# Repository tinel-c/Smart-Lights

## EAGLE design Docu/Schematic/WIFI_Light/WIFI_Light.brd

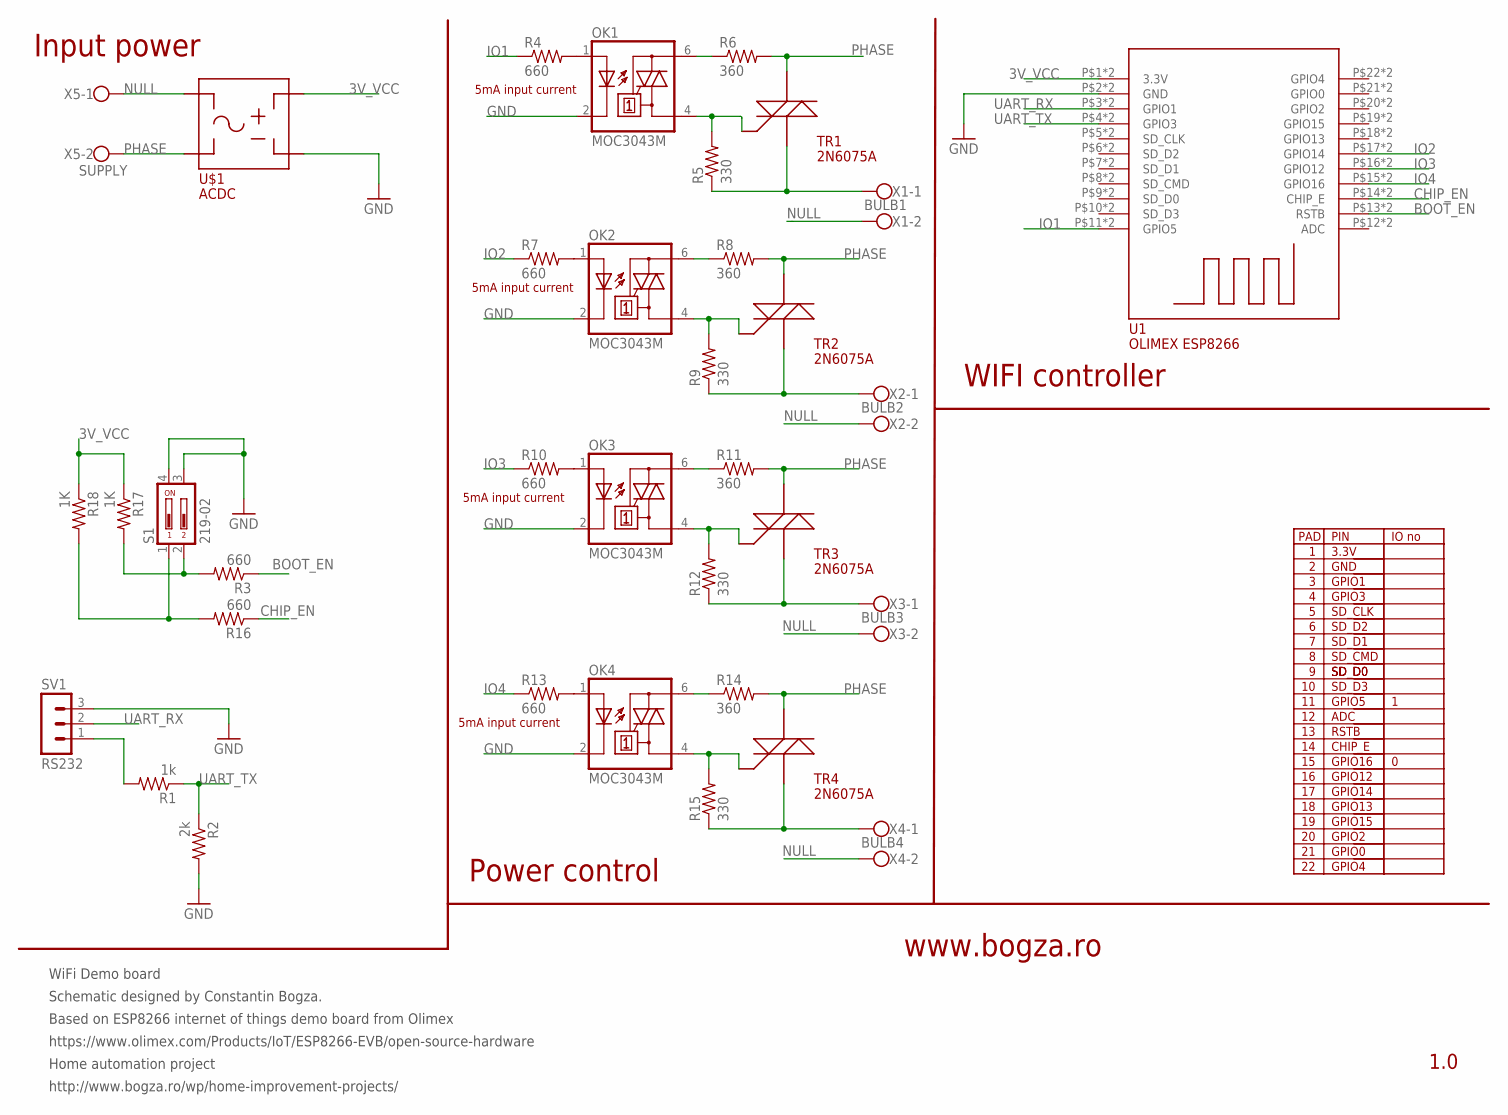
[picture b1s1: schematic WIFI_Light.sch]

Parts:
OK1, OK2, OK3, OK4: MOC3043M; DIL06
R1: 1k; 1206
R2: 2k; 1206
R3, R4, R7, R10, R13, R16: 660; 1206
R5, R9, R12, R15: 330; 1206
R6, R8, R11, R14: 360; 1206
R17, R18: 1K; 1206
S1: 219-02; CTS-219-02
SV1: RS232; MA03-1
TR1, TR2, TR3, TR4: 2N6071A/B; TO–225AA
U1: OLIMEX_ESP8266; OLIMEX_ESP8266_DIP22
U$1: ACDC_220V_3V3
X1: BULB1; W237-102
X2: BULB2; W237-102
X3: BULB3; W237-102
X4: BULB4; W237-102
X5: SUPPLY; W237-102

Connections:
3V_VCC: R17.1, R18.1, U1.P$1 (3.3V), U1.P$23 (3.3V), U$1.VCC
BOOT_EN: R3.1, U1.P$13 (RSTB), U1.P$35 (RSTB)
CHIP_EN: R16.1, U1.P$14 (CHIP_E), U1.P$36 (CHIP_E)
GND: OK1.2 (C), OK2.2 (C), OK3.2 (C), OK4.2 (C), R2.2, S1.3, S1.4, SV1.3, U1.P$2 (GND), U1.P$24 (GND), U$1.GND
IO1: R4.1, U1.P$11 (GPIO5), U1.P$33 (GPIO5)
IO2: R7.1, U1.P$17 (GPIO14), U1.P$39 (GPIO14)
IO3: R10.1, U1.P$16 (GPIO12), U1.P$38 (GPIO12)
IO4: R13.1, U1.P$15 (GPIO16), U1.P$37 (GPIO16)
unnamed: OK1.6 (A2), R6.1
unnamed: OK1.1 (A), R4.2
unnamed: R3.2, R17.2, S1.2
unnamed: R16.2, R18.2, S1.1
unnamed: OK1.4 (A1), R5.2, TR1.G
unnamed: OK2.6 (A2), R8.1
unnamed: R1.2, SV1.1
unnamed: OK2.1 (A), R7.2
unnamed: OK2.4 (A1), R9.2, TR2.G
unnamed: OK3.6 (A2), R11.1
unnamed: OK3.1 (A), R10.2
unnamed: OK3.4 (A1), R12.2, TR3.G
unnamed: OK4.6 (A2), R14.1
unnamed: OK4.1 (A), R13.2
unnamed: OK4.4 (A1), R15.2, TR4.G
NULL: U$1.PHASE, X1.2, X2.2, X3.2, X4.2, X5.1
OUT1: R5.1, TR1.MT1, X1.1
OUT2: R9.1, TR2.MT1, X2.1
OUT3: R12.1, TR3.MT1, X3.1
OUT4: R15.1, TR4.MT1, X4.1
PHASE: R6.2, R8.2, R11.2, R14.2, TR1.MT2, TR2.MT2, TR3.MT2, TR4.MT2, U$1.NULL, X5.2
UART_RX: SV1.2, U1.P$3 (GPIO1), U1.P$25 (GPIO1)
UART_TX: R1.1, R2.1, U1.P$4 (GPIO3), U1.P$26 (GPIO3)

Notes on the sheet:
WiFi Demo board
Schematic designed by Constantin Bogza.
Based on ESP8266 internet of things demo board from Olimex
Home automation project
http://www.bogza.ro/wp/home-improvement-projects/
https://www.olimex.com/Products/IoT/ESP8266-EVB/open-source-hardware
www.bogza.ro
1.0
PAD
GPIO1
GPIO3
SD_CLK
SD_D0
SD_D1
SD_D2
SD_D3
SD_CMD
3.3V
GND
GPIO5
GPIO4
GPIO0
GPIO2
GPIO15
GPIO13
GPIO12
GPIO14
GPIO16
ADC
PIN
RSTB
CHIP_E
IO no
5mA input current
Power control
WIFI controller
Input power

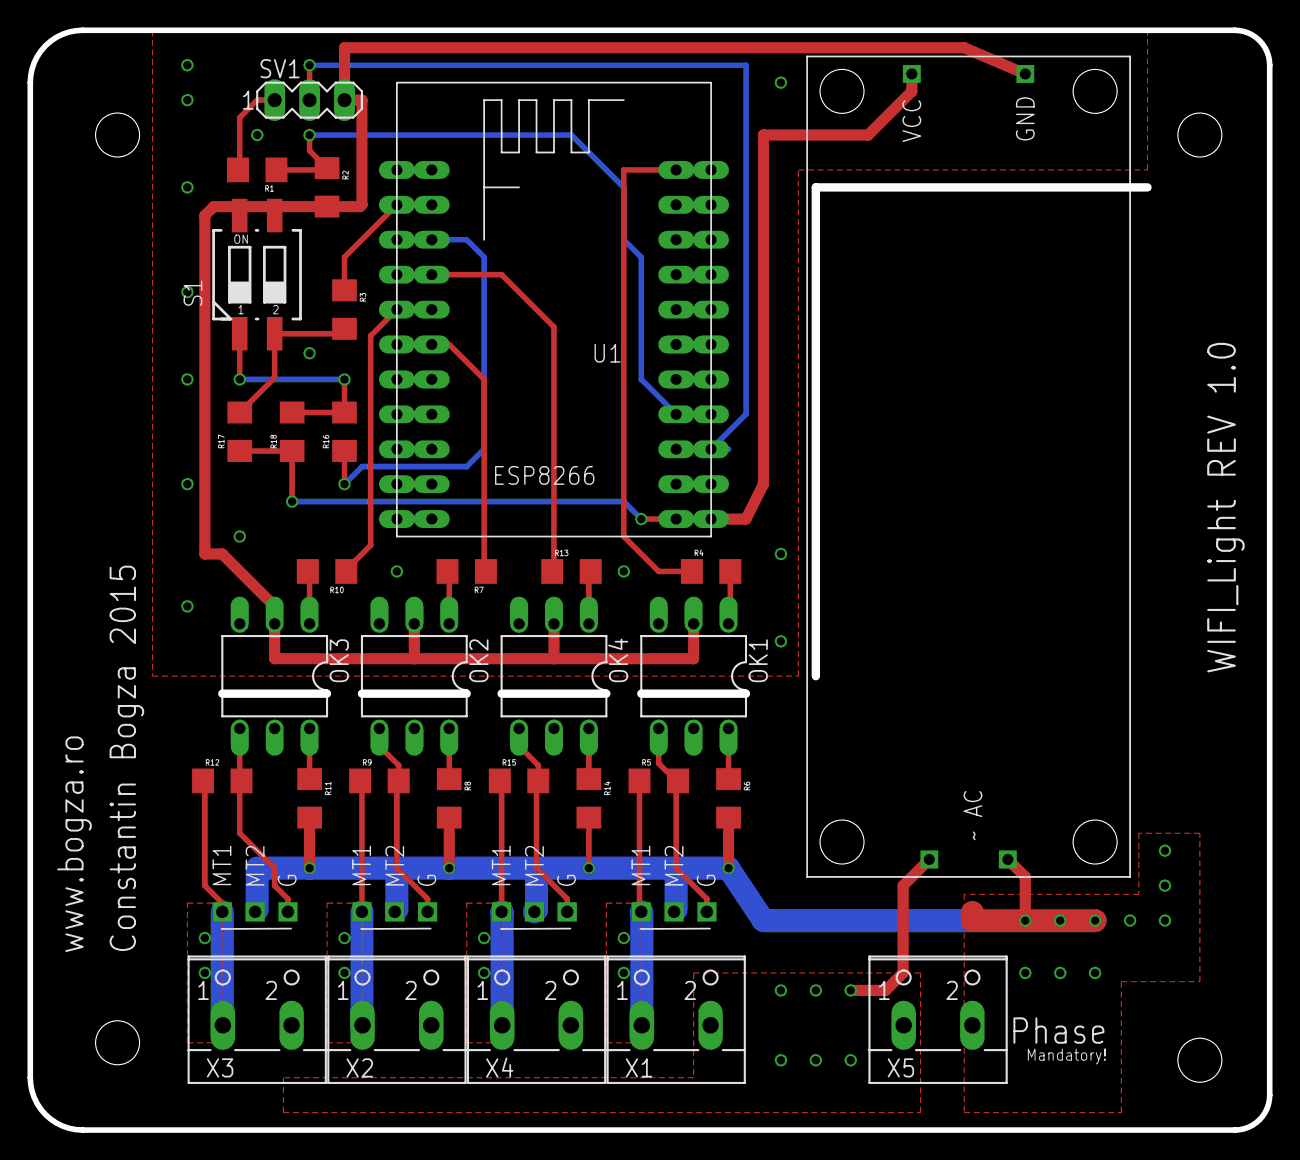
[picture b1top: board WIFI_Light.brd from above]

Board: 2 copper layers, 90.0 x 79.8 mm, 35 parts (0 on the bottom side), 31 nets.

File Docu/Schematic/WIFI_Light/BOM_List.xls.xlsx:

|  | Partlist
 |  | Exported | from | WIFI_Light.brd | at | 42129 | 0.50488425925925928 | AM
 |  | EAGLE | Version | 7.1.0 | Copyright | (c) | 1988-2014 | CadSoft
 |  | Assembly | variant:
 |  | Part | Value | Package | Library | Position | (inch) | Orientation | Price
 |  | PCB |  |  |  |  |  |  | 10
 |  | OK1 | MOC3043M | DIL06 | optocoupler | (1.9 | 1.3) | R180 | 1.43
 |  | OK2 | MOC3043M | DIL06 | optocoupler | (1.1 | 1.3) | R180 | 1.43
 |  | OK3 | MOC3043M | DIL06 | optocoupler | (0.7 | 1.3) | R180 | 1.43
 |  | OK4 | MOC3043M | DIL06 | optocoupler | (1.5 | 1.3) | R180 | 1.43
 |  | R1 | 1k | 1206 | SparkFun | (0.65 | 2.75) | R180 | 3.5000000000000003E-2
 |  | R2 | 2k | 1206 | SparkFun | (0.85 | 2.7) | R270 | 3.5000000000000003E-2
 |  | R3 | 660 | 1206 | SparkFun | (0.9 | 2.35) | R270 | 3.5000000000000003E-2
 |  | R4 | 660 | 1206 | SparkFun | (1.95 | 1.6) | R0 | 3.5000000000000003E-2
 |  | R5 | 330 | 1206 | SparkFun | (1.8 | 1) | R0 | 3.5000000000000003E-2
 |  | R6 | 360 | 1206 | SparkFun | (2 | 0.95) | R270 | 3.5000000000000003E-2
 |  | R7 | 660 | 1206 | SparkFun | (1.25 | 1.6) | R180 | 3.5000000000000003E-2
 |  | R8 | 360 | 1206 | SparkFun | (1.2 | 0.95) | R270 | 3.5000000000000003E-2
 |  | R9 | 330 | 1206 | SparkFun | (1 | 1) | R0 | 3.5000000000000003E-2
 |  | R10 | 660 | 1206 | SparkFun | (0.85 | 1.6) | R180 | 3.5000000000000003E-2
 |  | R11 | 360 | 1206 | SparkFun | (0.8 | 0.95) | R270 | 3.5000000000000003E-2
 |  | R12 | 330 | 1206 | SparkFun | (0.55 | 1) | R0 | 3.5000000000000003E-2
 |  | R13 | 660 | 1206 | SparkFun | (1.55 | 1.6) | R0 | 3.5000000000000003E-2
 |  | R14 | 360 | 1206 | SparkFun | (1.6 | 0.95) | R270 | 3.5000000000000003E-2
 |  | R15 | 330 | 1206 | SparkFun | (1.4 | 1) | R0 | 3.5000000000000003E-2
 |  | R16 | 660 | 1206 | SparkFun | (0.9 | 2) | R90 | 3.5000000000000003E-2
 |  | R17 | 1K | 1206 | SparkFun | (0.6 | 2) | R90 | 3.5000000000000003E-2
 |  | R18 | 1K | 1206 | SparkFun | (0.75 | 2) | R90 | 3.5000000000000003E-2
 |  | S1 | 219-02 | CTS-219-02 | switch-dil | (0.65 | 2.45) | R0 | 3.5000000000000003E-2
 |  | SV1 | RS232 | MA03-1 | con-lstb | (0.8 | 2.95) | R0 | 0.5
 |  | TR1 | 2N6071A/B | TO?225AA | Olimex_ESP8266 | (1.75 | 0.625) | R90 | 1.26
 |  | TR2 | 2N6071A/B | TO?225AA | Olimex_ESP8266 | (0.95 | 0.625) | R90 | 1.26
 |  | TR3 | 2N6071A/B | TO?225AA | Olimex_ESP8266 | (0.55 | 0.625) | R90 | 1.26
 |  | TR4 | 2N6071A/B | TO?225AA | Olimex_ESP8266 | (1.35 | 0.625) | R90 | 1.26
 |  | U$1 | ACDC_220V_3V3 | ACDC_220V_3V3 | Olimex_ESP8266 | (2.85 | 1.825) | R90 | 10
 |  | U1 | OLIMEX_ESP8266 | OLIMEX_ESP8266_DIP22 | Olimex_ESP8266 | (1.5 | 2.45) | R180 | 22
 |  | X1 | BULB1 | W237-102 | con-wago-500 | (1.85 | 0.35) | R0 | 0.5
 |  | X2 | BULB2 | W237-102 | con-wago-500 | (1.05 | 0.35) | R0 | 0.5
 |  | X3 | BULB3 | W237-102 | con-wago-500 | (0.65 | 0.35) | R0 | 0.5
 |  | X4 | BULB4 | W237-102 | con-wago-500 | (1.45 | 0.35) | R0 | 0.5
 |  | X5 | SUPPLY | W237-102 | con-wago-500 | (2.6 | 0.35) | R0 | 0.5
 |  |  |  |  |  |  |  |  | 56.425000000000011

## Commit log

2017-05-27 Initial version of the Smart-lights project. SML-1 Add to github the initial repository #time 4h #comment pushed to github #resolve
2017-05-27 SML-1 Add to github inital repository Remove password from github.
2017-07-24 adaugare test
